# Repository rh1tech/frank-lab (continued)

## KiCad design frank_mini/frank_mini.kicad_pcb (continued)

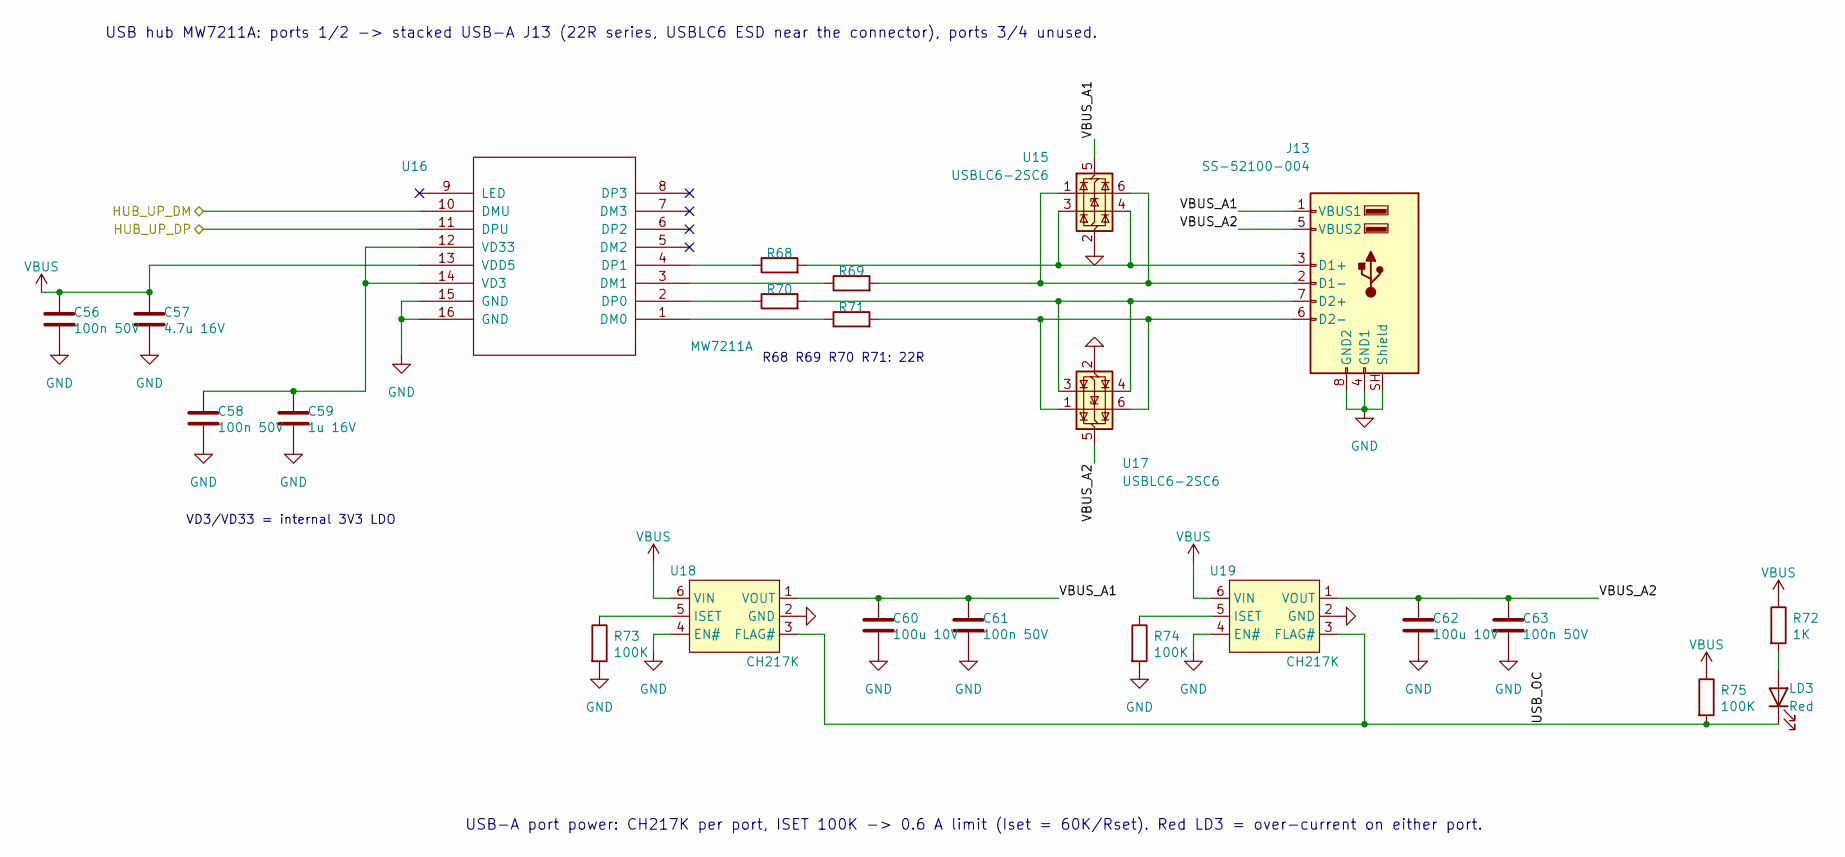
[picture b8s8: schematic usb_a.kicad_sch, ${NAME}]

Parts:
C56, C58, C61, C63: 100n 50V; C_0603_1608Metric
C57: 4.7u 16V; C_0603_1608Metric
C59: 1u 16V; C_0603_1608Metric
C60, C62: 100u 10V; C_1206_3216Metric
J13: SS-52100-004; USB_A_Stacked
LD3: Red; LED_0603_1608Metric
R68, R69, R70, R71: 22R; R_0603_1608Metric
R72: 1K; R_0603_1608Metric
R73, R74, R75: 100K; R_0603_1608Metric
U15, U17: USBLC6-2SC6; SOT-23-6
U16: MW7211A; SOP-16
U18, U19: CH217K; SOT-23-6

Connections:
/HUB_UP_DM: U16.10 (DMU); also elsewhere on the board
/HUB_UP_DP: U16.11 (DPU); also elsewhere on the board
/USB-A/USB_OC: LD3.1 (K), R75.2, U18.3 (FLAG#), U19.3 (FLAG#)
/USB-A/VBUS_A1: C60.1, C61.1, J13.1 (VBUS1), U15.5 (VBUS), U18.1 (VOUT)
/USB-A/VBUS_A2: C62.1, C63.1, J13.5 (VBUS2), U17.5 (VBUS), U19.1 (VOUT)
GND: C56.2, C57.2, C58.2, C59.2, C60.2, C61.2, C62.2, C63.2, J13.4 (GND1), J13.8 (GND2), J13.SH (Shield), R73.2, R74.2, U15.2 (GND), U16.15 (GND), U16.16 (GND), U17.2 (GND), U18.2 (GND), U18.4 (EN#), U19.2 (GND), U19.4 (EN#); also elsewhere on the board
unnamed: J13.3 (D1+), R68.2, U15.3 (I/O2), U15.4 (I/O2)
unnamed: J13.2 (D1-), R69.2, U15.1 (I/O1), U15.6 (I/O1)
unnamed: J13.7 (D2+), R70.2, U17.3 (I/O2), U17.4 (I/O2)
unnamed: J13.6 (D2-), R71.2, U17.1 (I/O1), U17.6 (I/O1)
unnamed: LD3.2 (A), R72.2
unnamed: R71.1, U16.1 (DM0)
unnamed: R69.1, U16.3 (DM1)
unnamed: R70.1, U16.2 (DP0)
unnamed: R68.1, U16.4 (DP1)
unnamed: C58.1, C59.1, U16.12 (VD33), U16.14 (VD3)
unnamed: R73.1, U18.5 (ISET)
unnamed: R74.1, U19.5 (ISET)
VBUS: C56.1, C57.1, R72.1, R75.1, U16.13 (VDD5), U18.6 (VIN), U19.6 (VIN); also elsewhere on the board

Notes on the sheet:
USB hub MW7211A: ports 1/2 -> stacked USB-A J13 (22R series, USBLC6 ESD near the connector), ports 3/4 unused.
VD3/VD33 = internal 3V3 LDO
R68 R69 R70 R71: 22R
USB-A port power: CH217K per port, ISET 100K -> 0.6 A limit (Iset = 60K/Rset). Red LD3 = over-current on either port.

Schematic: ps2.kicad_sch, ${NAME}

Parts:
C50, C51, C52: 100n 50V; C_0603_1608Metric
J11: MDC-036; MiniDIN_6pin_Female
U13: TXS0104EDR; SOIC-14_P1.27mm

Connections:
+3V3: C50.1, U13.1 (VCCA), U13.8 (OE); also elsewhere on the board
/M0_PS_MCLK_TX: U13.4 (A3); also elsewhere on the board
/M1_PS_MDAT_RX: U13.5 (A4); also elsewhere on the board
/M2_PS_KCLK: U13.2 (A1); also elsewhere on the board
/M3_PS_KDAT: U13.3 (A2); also elsewhere on the board
GND: C50.2, C51.2, C52.2, J11.3, U13.7 (GND); also elsewhere on the board
unnamed: J11.5, U13.13 (B1)
unnamed: J11.1, U13.12 (B2)
unnamed: J11.6, U13.11 (B3)
unnamed: J11.2, U13.10 (B4)
VBUS: C51.1, C52.1, J11.4, U13.14 (VCCB); also elsewhere on the board

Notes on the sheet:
PS/2 keyboard + mouse on one Mini-DIN (J11): TXS0104E 3V3 <-> 5V, OE tied high.
C50 VCCA, C51 VCCB at U13; C52 at the connector VBUS pin. U13 has internal 10K pull-ups on both sides.

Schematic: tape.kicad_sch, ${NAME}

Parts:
C47, C48: 100n 50V; C_0603_1608Metric
J9: PJ-320D; AudioJack_3.5mm_PJ320D_TapeIn
R54: 4.7K; R_0603_1608Metric
R55, R56: 100K; R_0603_1608Metric
U12: CD4069UBM; SOIC127P600X175-14N

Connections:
+3V3: C48.1, U12.14 (VDD); also elsewhere on the board
/TP_LOAD: U12.6 (I=*C); also elsewhere on the board
/Tape In/TAPE: C47.2, J9.T
GND: C48.2, J9.S, U12.7 (VSS), U12.9 (D14), U12.11 (E), U12.13 (F); also elsewhere on the board
unnamed: C47.1, R54.2
unnamed: R54.1, R55.2, U12.1 (A)
unnamed: R56.1, U12.3 (B)
unnamed: U12.4 (H=*B), U12.5 (C)
unnamed: R55.1, R56.2, U12.2 (G-*A)

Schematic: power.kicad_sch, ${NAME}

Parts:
C18, C21, C23, C24, C27, C28: 10u 16V; C_0603_1608Metric
C19: 1u 16V; C_0603_1608Metric
C20: 220u 10V; C_Radial_D6.3mm_P2.50mm
C22, C25: 100n 50V; C_0603_1608Metric
C26: 100u 10V; C_1206_3216Metric
C29: 22p 50V; C_0603_1608Metric
F1: 1.5A 6V; Fuse_1812_4532Metric; LCSC C262029
FB1: 600R@100MHz 2A; L_0805_2012Metric
JP4: Force On; SolderJumper-2_P1.3mm_Open_RoundedPad1.0x1.5mm
L2: 2.2u; L_Cenker_CKCS3015_HandSolder
LD2: Green; LED_0603_1608Metric
Q1, Q2: AO3401A; SOT-23-3L_AOS
R9: 100K; R_0603_1608Metric
R10: 10K; R_0603_1608Metric
R11: 1K; R_0603_1608Metric
R12: 100K 1%; R_0603_1608Metric
R13: 22K 1%; R_0603_1608Metric
S4: SK12D07VG3NS
TP1: VBUS_USB_F; TestPoint_Pad_D1.0mm
TP2: VBUS_USB; TestPoint_Pad_D1.0mm
TP3: +1V1; TestPoint_Pad_D1.0mm
TP4: +5V_BUCK; TestPoint_Pad_D1.0mm
TP5: LX; TestPoint_Pad_D1.0mm
U4: SY8089AAAC; SOT-23-5

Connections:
+1V1: TP3.1 (1_1); also elsewhere on the board
+3V3: C26.1, C27.1, C28.1, C29.1, L2.2, R11.1, R12.1; also elsewhere on the board
/Power/+5V_BUCK: C23.1, C24.1, C25.1, FB1.2, TP4.1 (1_1), U4.1 (EN), U4.4 (IN)
/Power/FB: C29.2, R12.2, R13.1, U4.5 (FB)
/Power/PWR_G: C19.2, Q1.1 (G), Q2.1 (G), R9.2, R10.1
/Power/VBUS_SW: C19.1, Q1.2 (S), Q2.2 (S), R9.1
/Power/VBUS_USB_F: C18.1, F1.2, Q1.3 (D), TP1.1 (1_1)
/VBUS_USB: F1.1, TP2.1 (1_1); also elsewhere on the board
GND: C18.2, C20.2, C21.2, C22.2, C23.2, C24.2, C25.2, C26.2, C27.2, C28.2, JP4.1 (A), LD2.1 (K), R13.2, S4.2, U4.2 (GND); also elsewhere on the board
unnamed: JP4.2 (B), R10.2, S4.1
unnamed: LD2.2 (A), R11.2
unnamed: L2.1, TP5.1 (1_1), U4.3 (LX)
VBUS: C20.1, C21.1, C22.1, FB1.1, Q2.3 (D); also elsewhere on the board

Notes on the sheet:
3V3: SY8089AAAC sync buck, Vout = 0.6 x (1 + R12/R13) = 3.33 V, C29 feed-forward.
S4 pulls PWR_G low; gate RC tau ~= (R9 || R10) x C19 = 9.1 ms. R9 returns the gates to the sources on turn-off; JP4 Force On bypasses S4. This is not a regulated current limiter; measure USB hot-plug inrush with the full load.
USB-C 5 V in: F1 polyfuse, Q1/Q2 back-to-back soft switch. Reverse blocking is OFF-state only; do not feed J1/VBUS while USB-C is connected.

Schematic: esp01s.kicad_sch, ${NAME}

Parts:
C53: 100n 50V; C_0603_1608Metric
C54: 10u 16V; C_0603_1608Metric
C55: 100u 10V; C_1206_3216Metric
R64, R65, R66, R67: 10K; R_0603_1608Metric
S5: ESP Boot; KMR_2
U14: ESP-01v090; ESP-01

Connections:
+3V3: C53.1, C54.1, C55.1, R64.1, R65.1, R66.1, R67.1, U14.7 (VCC); also elsewhere on the board
/ES_RST: R64.2, U14.5 (RST); also elsewhere on the board
/M20_ES_TX_GP: U14.8 (URXD); also elsewhere on the board
/M21_ES_RX_GP: U14.1 (UTXD); also elsewhere on the board
GND: C53.2, C54.2, C55.2, S5.1, S5.3, U14.2 (GND); also elsewhere on the board
unnamed: R65.2, U14.3 (CH_PD)
unnamed: R67.2, S5.2, S5.4, U14.6 (GPIO0)
unnamed: R66.2, U14.4 (GPIO2)

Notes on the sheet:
UART: TX = ESP UTXD -> RP GPIO21, RX = ESP URXD <- RP GPIO20 (shared with the gamepad port).
ESP-01 socket: 10K pull-ups keep EN/RST/GPIO0/GPIO2 high for normal boot; hold S5 "ESP Boot" + press ESP Reset to flash it.

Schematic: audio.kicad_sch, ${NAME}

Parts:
J7: Ext_Sound; IDC-Header_2x05_P2.54mm_Vertical
J8: PJ-320D; AudioJack_3.5mm_PJ320D_AudioOut

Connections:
+3V3: J7.10; also elsewhere on the board
/Audio Multiplexer/TS_OUT_L: J7.3; also elsewhere on the board
/Audio Multiplexer/TS_OUT_R: J7.5; also elsewhere on the board
/Audio/AMP_OUTL: J8.T; also elsewhere on the board
/Audio/AMP_OUTR: J8.R; also elsewhere on the board
/M9_AU_DATA: J7.4; also elsewhere on the board
/M10_AU_SCLK: J7.1; also elsewhere on the board
/M11_AU_LRCK: J7.2; also elsewhere on the board
GND: J7.7, J7.8, J7.9, J8.S; also elsewhere on the board
VBUS: J7.6; also elsewhere on the board

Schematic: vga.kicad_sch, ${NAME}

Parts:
J6: VGA; DSUB-15_Female
R31, R32, R33: 330R; R_0603_1608Metric
R34, R35, R36: 1K; R_0603_1608Metric
R37, R38: 100R; R_0603_1608Metric

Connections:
/M12_HV_CLK-_B0: R36.1; also elsewhere on the board
/M13_HV_CLK+_B1: R33.1; also elsewhere on the board
/M14_HV_D0-_G0: R35.1; also elsewhere on the board
/M15_HV_D0+_G1: R32.1; also elsewhere on the board
/M16_HV_D1-_R0: R34.1; also elsewhere on the board
/M17_HV_D1+_R1: R31.1; also elsewhere on the board
/M18_HV_D2-_HS: R37.2; also elsewhere on the board
/M19_HV_D2+_VS: R38.2; also elsewhere on the board
GND: J6.0, J6.5, J6.6, J6.7, J6.8, J6.10; also elsewhere on the board
unnamed: J6.1, R31.2, R34.2
unnamed: J6.2, R32.2, R35.2
unnamed: J6.3, R33.2, R36.2
unnamed: J6.13, R37.1
unnamed: J6.14, R38.1

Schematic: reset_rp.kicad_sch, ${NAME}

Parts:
S7: RP Reset; KMR_2; Mouser Part Number 611-KMR221G-LFS
S8: RP Reset; TS-1234VW

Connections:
/M_RUN: S7.2, S7.4, S8.1; also elsewhere on the board
GND: S7.1, S7.3, S8.2, S8.3 (GND); also elsewhere on the board

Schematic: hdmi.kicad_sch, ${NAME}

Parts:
C35: 100n 50V; C_0603_1608Metric
D1: 1N5819WS; D_SOD-323
J5: HDMI-001 19PCBTP; HDMI_Female; LCSC C138388
RN1, RN2: 270R; R_Array_4x0603; LCSC C1731063

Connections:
/M12_HV_CLK-_B0: RN1.4 (R4.1); also elsewhere on the board
/M13_HV_CLK+_B1: RN1.3 (R3.1); also elsewhere on the board
/M14_HV_D0-_G0: RN1.2 (R2.1); also elsewhere on the board
/M15_HV_D0+_G1: RN1.1 (R1.1); also elsewhere on the board
/M16_HV_D1-_R0: RN2.4 (R4.1); also elsewhere on the board
/M17_HV_D1+_R1: RN2.3 (R3.1); also elsewhere on the board
/M18_HV_D2-_HS: RN2.2 (R2.1); also elsewhere on the board
/M19_HV_D2+_VS: RN2.1 (R1.1); also elsewhere on the board
GND: C35.2, J5.2 (G_D2), J5.5 (G_D1), J5.8 (G_D0), J5.11 (G_CLK), J5.17 (G_DDC/CEC), J5.20 (SHIELD1), J5.21 (SHIELD2), J5.22 (SHIELD3), J5.23 (SHIELD4); also elsewhere on the board
unnamed: C35.1, D1.1 (K), J5.18 (+5V)
unnamed: J5.12 (CLKN), RN1.5 (R4.2)
unnamed: J5.10 (CLKP), RN1.6 (R3.2)
unnamed: J5.9 (D0N), RN1.7 (R2.2)
unnamed: J5.7 (D0P), RN1.8 (R1.2)
unnamed: J5.6 (D1N), RN2.5 (R4.2)
unnamed: J5.4 (D1P), RN2.6 (R3.2)
unnamed: J5.3 (D2N), RN2.7 (R2.2)
unnamed: J5.1 (D2P), RN2.8 (R1.2)
VBUS: D1.2 (A); also elsewhere on the board

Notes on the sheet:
RN1, RN2: 270R TMDS series

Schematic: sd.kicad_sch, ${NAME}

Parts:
C49: 100n 50V; C_0603_1608Metric
J10: 104031-0811; MicroSD_SMD_Long
R58, R59, R60: 10K; R_0603_1608Metric

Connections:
+3V3: C49.1, J10.4 (VDD), R58.1, R59.1, R60.1; also elsewhere on the board
/M4_SD_DAT0: J10.7 (DAT0), R58.2; also elsewhere on the board
/M5_SD_DAT3: J10.2 (DAT3/CD), R60.2; also elsewhere on the board
/M6_SD_CLK: J10.5 (CLK); also elsewhere on the board
/M7_SD_CMD: J10.3 (CMD), R59.2; also elsewhere on the board
GND: C49.2, J10.6 (VSS), J10.SH (SHIELD); also elsewhere on the board

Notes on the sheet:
10K pull-ups on CS, CMD, DAT0 (SPI); DAT1/DAT2 unused; C49 at the socket

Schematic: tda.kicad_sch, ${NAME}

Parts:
C36, C37: 10u 16V; C_0603_1608Metric
C38: 100n 50V; C_0603_1608Metric
R39: 100R; R_0603_1608Metric
R40, R41: 470R; R_0603_1608Metric
U9: TDA1387T; SO-8

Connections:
/Audio Multiplexer/TDA_L: R41.2, U9.6 (A_LEFT); also elsewhere on the board
/Audio Multiplexer/TDA_R: R40.1, U9.8 (A_RIGHT); also elsewhere on the board
/M9_AU_DATA: U9.3 (DATA); also elsewhere on the board
/M10_AU_SCLK: U9.1 (SCLK); also elsewhere on the board
/M11_AU_LRCK: U9.2 (LRCK); also elsewhere on the board
GND: C36.2, C37.2, C38.2, R40.2, R41.1, U9.4 (AGND); also elsewhere on the board
unnamed: C36.1, U9.7 (FLT)
unnamed: C37.1, C38.1, R39.1, U9.5 (VA)
VBUS: R39.2; also elsewhere on the board

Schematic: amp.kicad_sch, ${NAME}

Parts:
C39: 10u 16V; CP_EIA-3528-12_Kemet-T
C40: 100n 50V; C_0603_1608Metric
C41, C42, C43, C44, C45: 10u 16V; C_0603_1608Metric
R42, R43, R47, R49, R52: 10K; R_0603_1608Metric
R44: 100R; R_0603_1608Metric
R45, R46, R51: 20K; R_0603_1608Metric
R48, R50: 47K; R_0603_1608Metric
U10: LM358; SO-8

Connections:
/Audio Multiplexer/AMP_IN_L: C41.1, R42.1; also elsewhere on the board
/Audio Multiplexer/AMP_IN_R: C43.1, R43.1; also elsewhere on the board
/Audio/AMP_OUTL: C42.2, R46.2; also elsewhere on the board
/Audio/AMP_OUTR: C44.2, R51.2; also elsewhere on the board
GND: C39.2, C40.1, C45.1, R42.2, R43.2, R46.1, R51.1, R52.1, U10.4 (V-); also elsewhere on the board
unnamed: C41.2, R47.2
unnamed: C42.1, R48.1, U10.7
unnamed: C43.2, R49.2
unnamed: C44.1, R50.1, U10.1
unnamed: C45.2, R45.1, R52.2, U10.3 (+), U10.5 (+)
unnamed: R49.1, R50.2, U10.2 (-)
unnamed: R47.1, R48.2, U10.6 (-)
unnamed: C39.1, C40.2, R44.2, R45.2, U10.8 (V+)
VBUS: R44.1; also elsewhere on the board

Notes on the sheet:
LM358 is not rail-to-rail: R45/R52 bias at V+/3 to preserve positive output headroom. Line output only (>=10K load); not a headphone or speaker driver.

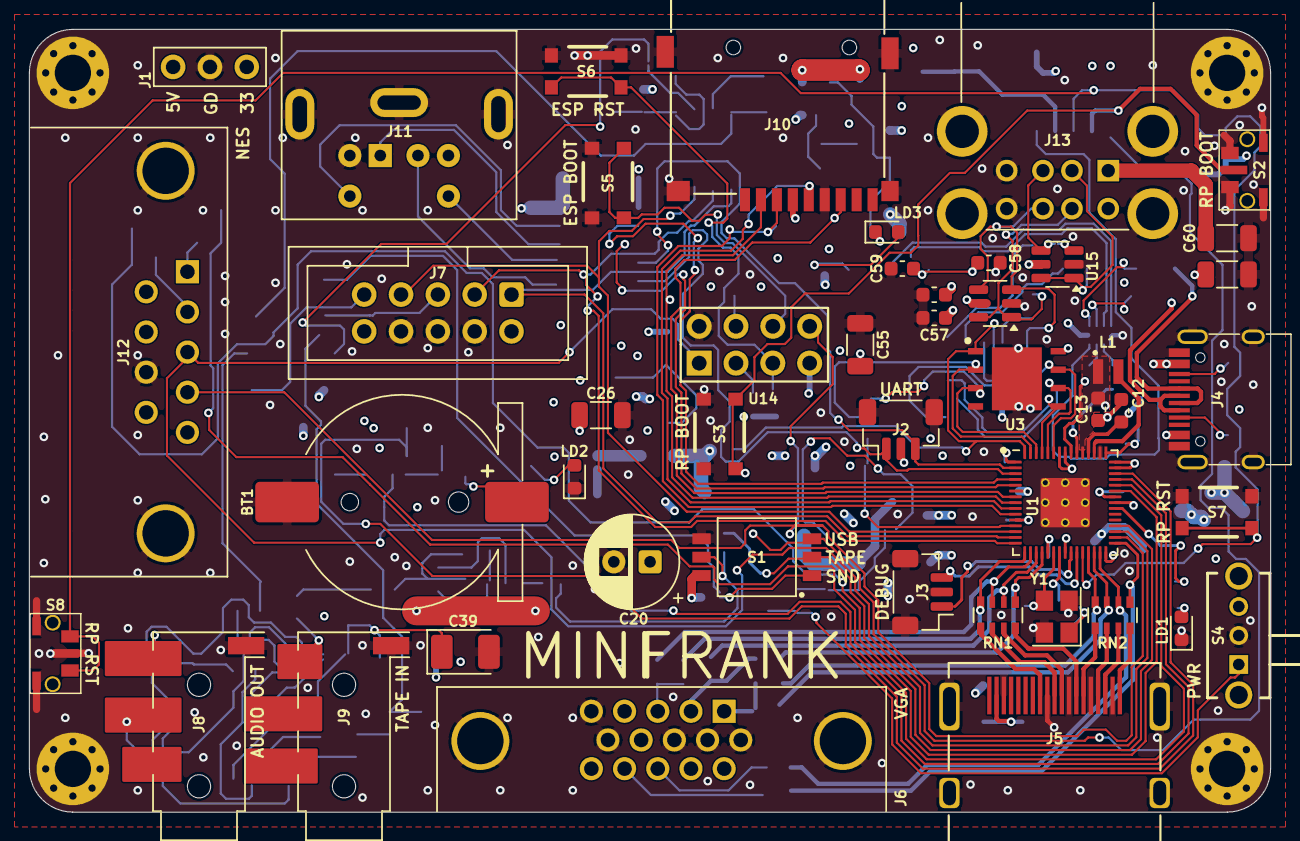
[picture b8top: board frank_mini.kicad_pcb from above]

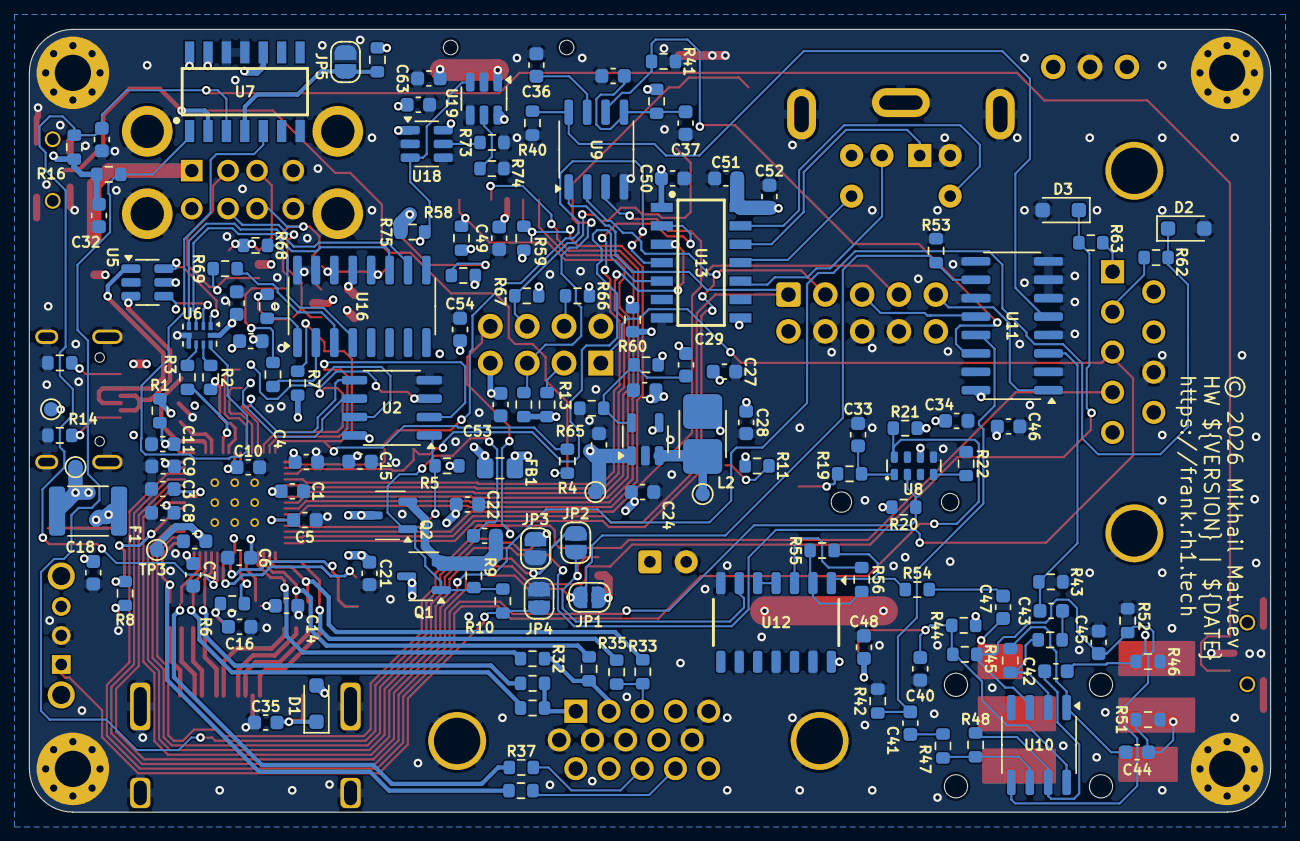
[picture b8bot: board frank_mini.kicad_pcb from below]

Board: 4 copper layers, 85.6 x 54.0 mm, 198 parts (148 on the bottom side), 140 nets.

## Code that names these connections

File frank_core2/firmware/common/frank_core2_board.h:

/*
 * FRANK Core 2 — dual-RP2350 test firmware
 *
 * Copyright (c) 2026 Mikhail Matveev <xtreme@rh1.tech>
 * https://github.com/rh1tech/frank
 * SPDX-License-Identifier: GPL-3.0-or-later
 */

/*
 * frank_core2_board.h — GPIO map for the FRANK Core 2 board.
 *
 * Every assignment below was extracted from the KiCad netlist
 * (frank_core2.kicad_sch -> kicad-cli sch export netlist), so this file
 * is the single source of truth shared by the master and slave builds.
 *
 * U3 = RP2350B (master, QFN-80)   U6 = RP2350  (slave, QFN-60)
 *
 * The master carries all the user-facing peripherals: HDMI (J5), microSD
 * (J7), TDA1387 I2S DAC (U8), USB-C host/device (J8), WS2812B status LED
 * (LD1) and 8 MB PSRAM (U2) + 16 MB flash (U1).
 *
 * The slave carries its own 8 MB PSRAM (U5) + 16 MB flash (U4), a USB-C
 * port (J9), a blue status LED (LD2) and a UART header (J4). Everything
 * else it needs it gets over the inter-processor link.
 */
#ifndef FRANK_CORE2_BOARD_H
#define FRANK_CORE2_BOARD_H

/* =====================================================================
 * Inter-processor link
 *
 * Two independent 8-bit source-synchronous buses, each with its own
 * clock and VALID strobe, plus three single-wire control signals.
 *
 *   Bus A  master -> slave   M.GPIO20..27 -> S.GPIO1..8
 *                            M.GPIO28 (CLK, 33R R1) -> S.GPIO9
 *                            M.GPIO29 (VALID)       -> S.GPIO10
 *
 *   Bus B  slave -> master   S.GPIO11..18 -> M.GPIO30..37
 *                            S.GPIO19 (CLK, 33R R2) -> M.GPIO38
 *                            S.GPIO20 (VALID)       -> M.GPIO39
 *
 * Both buses share the same relative layout, which the PIO programs
 * rely on: CLK == DATA_BASE + 8, VALID == DATA_BASE + 9. That lets one
 * pair of PIO programs serve both directions on both chips with nothing
 * but a different pin base.
 *
 * Control signals (plain SIO, no PIO):
 *   FS      M.GPIO40 -> S.GPIO21   frame-sync / phase strobe (master out)
 *   DB_MS   M.GPIO41 -> S.GPIO22   doorbell, master -> slave
 *   DB_SM   M.GPIO42 <- S.GPIO23   doorbell, slave  -> master
 *
 * NOTE ON GPIO43: the schematic labels M.GPIO43 as "RUNA/SR" (slave
 * reset), but the net only reaches a 10K pull-up to +3V3 (R3) — it is
 * NOT wired to the slave's RUN pin (U6.26), which only sees reset
 * button S4. The firmware therefore cannot reset the slave in hardware;
 * both MCUs must be reset/flashed independently. See README.md.
 * ===================================================================== */

/* ---- Master side (RP2350B / U3) ---- */
#define M_LINK_A_DATA_BASE   20   /* GPIO20..27, master -> slave  */
#define M_LINK_A_CLK         28   /* == DATA_BASE + 8             */
#define M_LINK_A_VALID       29   /* == DATA_BASE + 9             */

#define M_LINK_B_DATA_BASE   30   /* GPIO30..37, slave -> master  */
#define M_LINK_B_CLK         38
#define M_LINK_B_VALID       39

#define M_LINK_FS            40   /* out */
#define M_LINK_DB_OUT        41   /* DB_MS, out */
#define M_LINK_DB_IN         42   /* DB_SM, in  */
#define M_LINK_SLAVE_RUN     43   /* pull-up only — not connected, see above */

/* ---- Slave side (RP2350 / U6) ---- */
#define S_LINK_A_DATA_BASE    1   /* GPIO1..8, master -> slave (RX) */
#define S_LINK_A_CLK          9
#define S_LINK_A_VALID       10

#define S_LINK_B_DATA_BASE   11   /* GPIO11..18, slave -> master (TX) */
#define S_LINK_B_CLK         19
#define S_LINK_B_VALID       20

#define S_LINK_FS            21   /* in  */
#define S_LINK_DB_IN         22   /* DB_MS, in  */
#define S_LINK_DB_OUT        23   /* DB_SM, out */

/* =====================================================================
 * Master peripherals
 * ===================================================================== */

/* HDMI (J5) via HSTX — clock pair first, N before P, matches Murmulator 2 */
#define HDMI_BASE_PIN        12
#define HDMI_PIN_CLKN        12
#define HDMI_PIN_CLKP        13
#define HDMI_PIN_D0N         14
#define HDMI_PIN_D0P         15
#define HDMI_PIN_D1N         16
#define HDMI_PIN_D1P         17
#define HDMI_PIN_D2N         18
#define HDMI_PIN_D2P         19

/* microSD (J7) on SPI0 — SDIO pin names from the schematic in comments */
#define SDCARD_PIN_SPI0_MISO  4   /* SD DAT0    */
#define SDCARD_PIN_SPI0_CS    5   /* SD DAT3/CD */
#define SDCARD_PIN_SPI0_SCK   6   /* SD CLK     */
#define SDCARD_PIN_SPI0_MOSI  7   /* SD CMD     */

/* TDA1387T I2S DAC (U8) */
#define I2S_DATA_PIN          9   /* U8.3 DATA */
#define I2S_CLOCK_PIN_BASE   10   /* U8.1 SCLK = 10, U8.2 LRCK = 11 */

/* WS2812B status LED (LD1) via 330R R11 */
#define M_LED_WS2812_PIN     46

/* 8 MB PSRAM (U2 ESP-PSRAM64H) chip select */
#define M_PSRAM_CS_PIN       47

/* Debug UART header J2: pin1 = GPIO0 (TX), pin2 = GND, pin3 = GPIO1 (RX) */
#define M_UART_ID            uart0
#define M_UART_TX_PIN         0
#define M_UART_RX_PIN         1

/* Spare / unrouted master GPIOs (available for probing) */
#define M_SPARE_GPIO_LIST    { 2, 3, 8, 44, 45 }

/* =====================================================================
 * Slave peripherals
 * ===================================================================== */

/* 8 MB PSRAM (U5 ESP-PSRAM64H) chip select */
#define S_PSRAM_CS_PIN        0

/* Blue status LED (LD2) via 1K R19 — active high */
#define S_LED_PIN            26

/* Debug UART header J4: pin1 = GPIO24 (TX), pin2 = GND, pin3 = GPIO25 (RX) */
#define S_UART_ID            uart1
#define S_UART_TX_PIN        24
#define S_UART_RX_PIN        25

/* Spare / unrouted slave GPIOs */
#define S_SPARE_GPIO_LIST    { 27, 28, 29 }

/* =====================================================================
 * Memory devices (identical part numbers on both sides)
 * ===================================================================== */
#define FRANK_FLASH_PART     "W25Q128JVPIQ"
#define FRANK_FLASH_BYTES    (16u * 1024u * 1024u)
#define FRANK_PSRAM_PART     "ESP-PSRAM64H"
#define FRANK_PSRAM_BYTES    (8u * 1024u * 1024u)

/* XIP windows: CS0 = flash, CS1 = PSRAM (psram_init maps it there).
 *
 * The 0x14000000 aliases bypass the XIP cache entirely. That matters for
 * the PSRAM presence and size probes: through the cached window a write
 * followed by a read of the same address is answered out of the 8 KiB
 * cache, so a missing chip looks present and an address that aliases
 * back onto offset 0 looks like it does not. Throughput measurements
 * deliberately use the cached window, because that is how real code
 * reaches these devices. */
#define FRANK_XIP_FLASH_BASE         0x10000000u
#define FRANK_XIP_PSRAM_BASE         0x11000000u
#define FRANK_XIP_FLASH_NOCACHE_BASE 0x14000000u
#define FRANK_XIP_PSRAM_NOCACHE_BASE 0x15000000u

#endif /* FRANK_CORE2_BOARD_H */

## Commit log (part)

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2026-04-22 Initial commit: experimental boards from murmulator lab
2026-04-22 Add FRANK M2 v2.07 from murmulator dev branch
2026-04-23 FRANK M2 Updates
2026-04-23 FRANK M2 WIP
2026-04-23 FRANK HW 2.07
2026-04-23 FRANK M2 HW 2.07 Release
2026-04-23 Board updates
2026-04-28 FRANK Pro 1.01 HW Release
2026-04-28 Repo cleanup
2026-04-28 chore: remove tracked .DS_Store files
2026-05-01 Nyx WIP
2026-05-02 Nyx Release HW 2.00
2026-05-04 Nyx renamed
2026-05-04 Cleanup
2026-05-07 Lab updates
2026-05-12 docs: link to frank.rh1.tech in README
2026-05-14 Nyx updates
2026-05-15 xt8086 WIP
2026-05-15 xt8086 1.03
2026-05-19 FRANK Air WIP
2026-05-21 Complete boards cleanup
2026-05-25 FRANK_MEGA WIP
2026-05-26 FRANK MEGA WIP
2026-05-29 New boards WIP
2026-05-29 FRANK AIR 1.00
2026-05-30 FRANK MEGA (HW 1.00)
2026-05-30 Nyx HW 2.02 - moved to frank repo
2026-05-31 FRANK MEGA HW 1.00
2026-05-31 Protea board added
2026-05-31 Protea update
2026-06-01 Protea 2.00 WIP
2026-06-02 Protea updates
2026-06-04 docs: standardize naming (assembly.pdf, bom.html, schematics.pdf)
    Latest versions:
    - frank_mega: 1.01
    - frank_air: 1.01
    - protea: 2.00
2026-06-08 MiniFRANK WIP
2026-06-09 FRANK TurboSound WIP
2026-06-09 FRANK TurboSound Module HW 2.00
2026-06-15 Hecate updates
2026-06-15 Hecate 3.00
2026-06-28 Minor updates
2026-06-28 MiniFRANK moved to main repo
2026-06-28 refactor: move turbosound, megafrank, zerofrank and hecate to murmulator
    These KiCad projects graduate from frank-lab into the maintained frank
    (murmulator) repository:
    - frank_turbosound -> turbosound (child sheet -> turbosound_ay)
    - frank_mega -> megafrank
    - frank_zero -> zerofrank
    - hecate (USB-to-PS/2 bridge board)
